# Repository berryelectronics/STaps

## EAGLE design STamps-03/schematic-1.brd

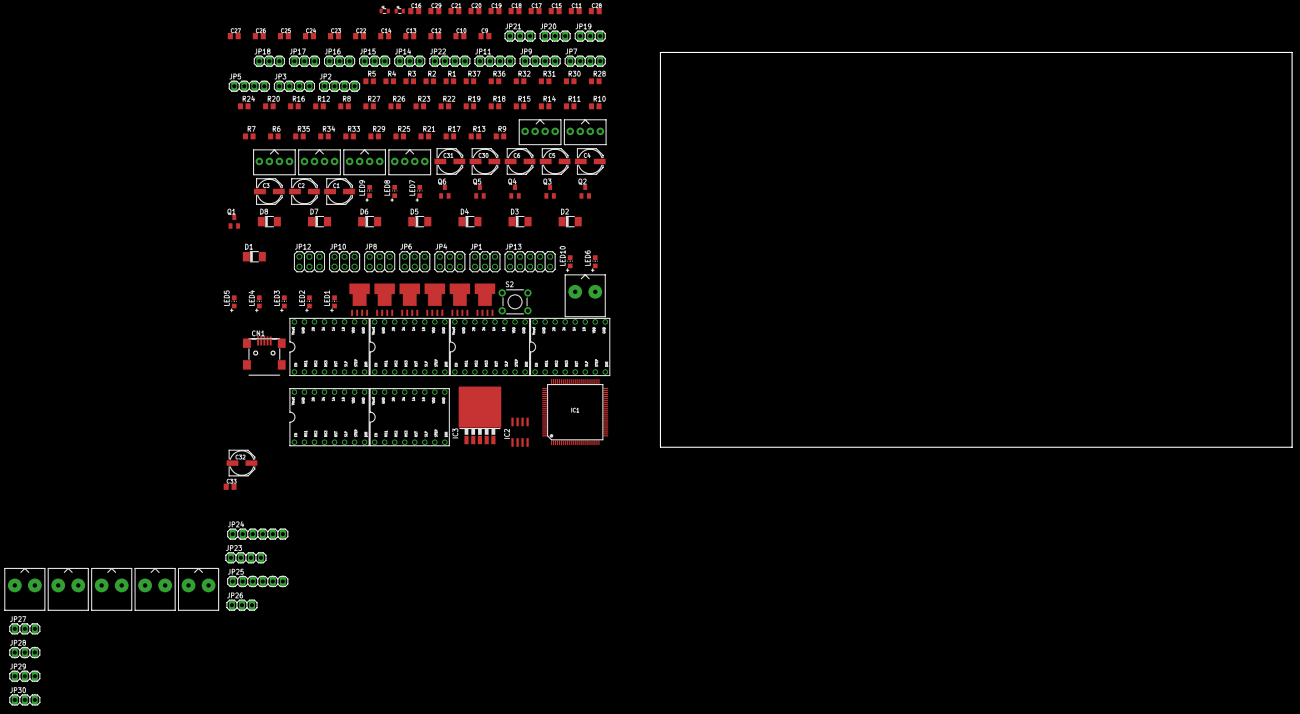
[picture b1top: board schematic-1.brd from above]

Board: 2 copper layers, 160.0 x 100.0 mm, 153 parts (0 on the bottom side), 141 nets, no tracks yet.

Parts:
C1, C2, C3, C4, C5, C6, C30, C31, C32: 100uF; PANASONIC_D
C9, C10, C12, C13, C14, C22, C23, C24, C25, C26, C27, C28, C33: 100nF; C0805K
C11: 4.7uF; C0805K
C15, C29: 10nF; C0805K
C16: 1uF; C0805K
C17, C18, C19, C20, C21: 10uF; C0805K
CN1: USB-MINIB
D1, D2, D3, D4, D5, D6, D7: 1N400x-SMD; DO-214AC
D8: 1N5820; DO-214AC
IC1: STM32F10XV; LQFP100-14MM
IC2: LT1763CS8-3.3; SOIC8
IC3: TO263-5
JP1, JP4, JP6, JP8, JP10, JP12: 2X03
JP2, JP3, JP5, JP7, JP9, JP11, JP22, JP23: 1X04
JP13: 2X05
JP14, JP15, JP16, JP17, JP18, JP19, JP20, JP21, JP26, JP27, JP28, JP29, JP30: 1X03
JP24, JP25: 1X06
JS1, JS2, JS3, JS4, JS5, JS6: PINHEAD-4PIN
JS7, JS8, JS9, JS10, JS11, JS12: PINHEAD-2PIN-HP
L1: 10uH; 0805
L2: 100uH; 0805
LED1, LED2, LED3, LED4, LED5, LED6: WHITE; CHIP-LED0805
LED7, LED8, LED9, LED10: RED; CHIP-LED0805
Q1, Q2, Q3, Q4, Q5, Q6: BSH105; SOT23
R1, R2, R3, R4, R5: 4k7; R0805
R6, R7, R10, R11, R14, R15, R18, R19, R22, R23, R26, R27: 100k; R0805
R8, R12, R16, R20, R24, R28: 10R; R0805
R9, R13, R17, R21, R25, R29, R33, R34: 180R; R0805
R30, R31: 22R; R0805
R32: 1k; R0805
R35: 100R; R0805
R36: 10K; R0805
R37: 3K3; R0805
S2: SWITCH-MOMENTARY-2PTH; TACTILE-PTH
T1, T2, T3, T4, T5, T6: PSMN7R0-30YL; SOT669
U$1, U$2, U$3, U$4, U$5, U$6: POLOLU_A4983CARRIER; A4988BREAKOUT

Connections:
3.3V: C9.1, C10.1, C11.1, C12.1, C13.1, C14.1, C30.+, IC1.P$11, IC1.P$28, IC1.P$50, IC1.P$75, IC1.P$100, IC2.1, JP14.1, JP15.1, JP16.1, JP17.1, JP18.1, JP19.1, JP20.1, JP21.1, JP23.4, JP24.6, JP26.1, L1.1, R1.2, R2.2, R3.2, R4.2, R5.2, R6.2, R10.2, R14.2, R18.2, R22.2, R26.2, R35.1, U$1.VDD, U$2.VDD, U$3.VDD, U$4.VDD, U$5.VDD, U$6.VDD
5V: C32.+, D7.C, IC2.5, IC2.8, JP1.2, JP1.4, JP1.6, JP4.2, JP4.4, JP4.6, JP6.2, JP6.4, JP6.6, JP8.2, JP8.4, JP8.6, JP10.2, JP10.4, JP10.6, JP12.2, JP12.4, JP12.6, JP26.3, L2.2, R7.2, R9.1, R11.2, R13.1, R15.2, R17.1, R19.2, R21.1, R23.2, R25.1, R27.2, R29.1, R34.1, R36.2
12V: C1.+, C2.+, C3.+, C4.+, C5.+, C6.+, C31.+, C33.1, D1.C, D2.C, D3.C, D4.C, D5.C, D6.C, IC3.1, JS7.1, JS8.1, JS9.1, JS10.1, JS11.1, JS12.1, R32.1, U$1.VMOT, U$2.VMOT, U$3.VMOT, U$4.VMOT, U$5.VMOT, U$6.VMOT
BED_LED: LED1.C, R8.2, T1.4
BL_RX: IC1.P$79, JP25.3
BL_TX: IC1.P$78, JP25.2
BOOT0: IC1.P$94, JP15.2
BOOT1: IC1.P$37, JP21.2
E0: IC1.P$25, Q2.1, R10.1
E0_DIR: IC1.P$56, U$3.DIR
E0_EN: IC1.P$46, U$3.EN
E0_LED: LED2.C, R12.2, T2.4
E0_OUTPUT: D1.A, JS8.2, T2.MB
E0_STEP: IC1.P$55, U$3.STEP
E1: IC1.P$35, Q3.1, R14.1
E1_DIR: IC1.P$45, U$1.DIR
E1_EN: IC1.P$43, U$1.EN
E1_LED: LED3.C, R16.2, T3.4
E1_OUTPUT: D3.A, JS9.2, T3.MB
E1_STEP: IC1.P$44, U$1.STEP
E2: IC1.P$36, Q4.1, R18.1
E2_DIR: IC1.P$42, U$2.DIR
E2_EN: IC1.P$40, U$2.EN
E2_LED: LED4.C, R20.2, T4.4
E2_OUTPUT: D4.A, JS10.2, T4.MB
E2_STEP: IC1.P$41, U$2.STEP
EXTRA0: IC1.P$63, Q5.1, R22.1
EXTRA0_LED: LED5.C, R24.2, T5.4
EXTRA0_OUTPUT: D5.A, JS11.2, T5.MB
EXTRA1: IC1.P$64, Q6.1, R26.1
EXTRA1_LED: LED6.C, R28.2, T6.4
EXTRA1_OUTPUT: D6.A, JS12.2, T6.MB
GND: C1.-, C2.-, C3.-, C4.-, C5.-, C6.-, C9.2, C10.2, C11.2, C12.2, C13.2, C14.2, C15.1, C16.1, C17.2, C18.2, C19.2, C20.2, C21.2, C22.1, C23.1, C24.1, C25.1, C26.1, C27.1, C28.1, C30.-, C31.-, C32.-, C33.2, CN1.GND, D8.A, IC1.P$10, IC1.P$19, IC1.P$20, IC1.P$27, IC1.P$49, IC1.P$74, IC1.P$99, IC2.3, IC2.6, IC2.7, IC3.3, IC3.5, IC3.6, JP13.2, JP13.4, JP13.6, JP13.8, JP13.10, JP14.2, JP15.3, JP16.2, JP17.2, JP18.2, JP19.2, JP20.2, JP21.3, JP23.1, JP24.4, JP25.4, JP27.1, JP28.1, JP29.1, JP30.1, LED7.C, LED8.C, LED9.C, LED10.C, Q1.2, Q2.2, Q3.2, Q4.2, Q5.2, Q6.2, R37.1, S2.3, T1.1, T1.2, T1.3, T2.1, T2.2, T2.3, T3.1, T3.2, T3.3, T4.1, T4.2, T4.3, T5.1, T5.2, T5.3, T6.1, T6.2, T6.3, U$1.GND, U$1.GND@0, U$2.GND, U$2.GND@0, U$3.GND, U$3.GND@0, U$4.GND, U$4.GND@0, U$5.GND, U$5.GND@0, U$6.GND, U$6.GND@0
HEATBED: IC1.P$24, Q1.1, R6.1
HEATBED_OUTPUT: D2.A, JS7.2, T1.MB
unnamed: JP1.1, U$2.MS1
unnamed: JP1.3, U$2.MS2
unnamed: JP1.5, U$2.MS3
unnamed: U$2.RST, U$2.SLP
unnamed: JP2.1, JS6.4, U$2.1B
unnamed: JP2.2, JS6.3, U$2.1A
unnamed: JP2.3, JS6.2, U$2.2A
unnamed: JP2.4, JS6.1, U$2.2B
unnamed: JP4.1, U$1.MS1
unnamed: JP4.3, U$1.MS2
unnamed: JP4.5, U$1.MS3
unnamed: U$1.RST, U$1.SLP
unnamed: JP5.1, JS5.4, U$1.1B
unnamed: JP5.2, JS5.3, U$1.1A
unnamed: JP5.3, JS5.2, U$1.2A
unnamed: JP5.4, JS5.1, U$1.2B
unnamed: JP6.1, U$3.MS1
unnamed: JP6.3, U$3.MS2
unnamed: JP6.5, U$3.MS3
unnamed: U$3.RST, U$3.SLP
unnamed: JP7.1, JS4.4, U$3.1B
unnamed: JP7.2, JS4.3, U$3.1A
unnamed: JP7.3, JS4.2, U$3.2A
unnamed: JP7.4, JS4.1, U$3.2B
unnamed: JP8.1, U$4.MS1
unnamed: JP8.3, U$4.MS2
unnamed: JP8.5, U$4.MS3
unnamed: U$4.RST, U$4.SLP
unnamed: JP9.1, JS3.4, U$4.1B
unnamed: JP9.2, JS3.3, U$4.1A
unnamed: JP9.3, JS3.2, U$4.2A
unnamed: JP9.4, JS3.1, U$4.2B
unnamed: JP10.1, U$5.MS1
unnamed: JP10.3, U$5.MS2
unnamed: JP10.5, U$5.MS3
unnamed: U$5.RST, U$5.SLP
unnamed: JP11.1, JS2.4, U$5.1B
unnamed: JP11.2, JS2.3, U$5.1A
unnamed: JP11.3, JS2.2, U$5.2A
unnamed: JP11.4, JS2.1, U$5.2B
unnamed: JP12.1, U$6.MS1
unnamed: JP12.3, U$6.MS2
unnamed: JP12.5, U$6.MS3
unnamed: U$6.RST, U$6.SLP
unnamed: JP3.1, JP22.1, JS1.4, U$6.1B
unnamed: JP3.2, JP22.2, JS1.3, U$6.1A
unnamed: JP3.3, JP22.3, JS1.2, U$6.2A
unnamed: JP3.4, JP22.4, JS1.1, U$6.2B
unnamed: LED1.A, R9.2
unnamed: C15.2, C16.2, IC1.P$21, IC1.P$22, L1.2
unnamed: C29.1, IC2.4
unnamed: IC3.4, R36.1, R37.2
unnamed: CN1.D-, R31.1
unnamed: CN1.D+, R30.1
unnamed: C29.2, IC2.2
unnamed: LED7.A, R32.2
unnamed: LED8.A, R33.2
unnamed: Q1.3, R7.1, R8.1
unnamed: D8.C, IC3.2, L2.1
unnamed: LED9.A, R34.2
unnamed: LED10.A, R35.2
unnamed: JP25.5, JP26.2
unnamed: Q4.3, R19.1, R20.1
unnamed: Q5.3, R23.1, R24.1
unnamed: LED6.A, R29.2
unnamed: LED5.A, R25.2
unnamed: Q6.3, R27.1, R28.1
unnamed: Q3.3, R15.1, R16.1
unnamed: Q2.3, R11.1, R12.1
unnamed: LED4.A, R21.2
unnamed: LED3.A, R17.2
unnamed: LED2.A, R13.2
unnamed: JP27.2, JP29.2, JP30.2
NRST: C28.2, IC1.P$14, JP24.2, S2.1
SERVO0: IC1.P$85, JP27.3
SERVO1: IC1.P$86, JP28.3
SERVO2: IC1.P$87, JP29.3
SERVO3: IC1.P$88, JP30.3
SWCLK: IC1.P$76, JP24.5
SWDIO: IC1.P$72, JP24.3
SWO: IC1.P$89, JP24.1
T0: C21.1, IC1.P$15, JP13.1, R5.1
T1: C20.1, IC1.P$16, JP13.3, R4.1
T2: C17.1, IC1.P$17, JP13.5, R2.1
T3: C18.1, IC1.P$18, JP13.7, R1.1
T4: C19.1, IC1.P$23, JP13.9, R3.1
USART1_RX: IC1.P$69, JP23.2
USART1_TX: IC1.P$68, JP23.3
USBDM: IC1.P$70, R31.2
USBDP: IC1.P$71, R30.2
VCC_1: CN1.VBUS, D7.A, R33.1
X-MAX: C23.2, IC1.P$1, JP16.3
X-MIN: C22.2, IC1.P$98, JP14.3
X_DIR: IC1.P$62, U$5.DIR
X_EN: IC1.P$60, U$5.EN
X_STEP: IC1.P$61, U$5.STEP
Y-MAX: C25.2, IC1.P$3, JP18.3
Y-MIN: C24.2, IC1.P$2, JP17.3
Y_DIR: IC1.P$59, U$4.DIR
Y_EN: IC1.P$57, U$4.EN
Y_STEP: IC1.P$58, U$4.STEP
Z-MAX: C27.2, IC1.P$5, JP20.3
Z-MIN: C26.2, IC1.P$4, JP19.3
Z_DIR: IC1.P$84, U$6.DIR
Z_EN: IC1.P$80, U$6.EN
Z_STEP: IC1.P$83, U$6.STEP

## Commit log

2016-01-21 :confetti_ball: Added .gitattributes & .gitignore files
2016-01-21 Init Release
    ~Straw
2016-01-22 Added PDF Files
    PDF Files for Eagle schematics, nothing new for KiCad ATM
2016-01-23 changes to kicad
2016-01-23 KiCad Changes
    Added some stuff

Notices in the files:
parts and their libraries:
SparkFun-Capacitors: Licensing: Creative Commons ShareAlike 4.0 International - https://creativecommons.org/licenses/by-sa/4.0
